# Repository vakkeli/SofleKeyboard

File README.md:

# Sofle Keyboard Vakkeli fork

Own version off the great keyboard. Added 7th column to better support ISO and Nordic layout. Will be updating this readme. PCB is in prototype production at this point. Hopefully adding 3D printed plates, case and models for them.

# Original Sofle Keyboard

Sofle is 6×4+5 keys column-staggered split keyboard with encoder support. Based on [Lily58](https://github.com/kata0510/Lily58), [Corne](https://github.com/foostan/crkbd) and [Helix](https://github.com/MakotoKurauchi/helix) keyboards.

**[For more information and documentation visit https://josefadamcik.github.io/SofleKeyboard/](https://josefadamcik.github.io/SofleKeyboard/)**

SofleKeyboard was created by [Josef Adamcik](https://josef-adamcik.cz/). The motivation and process is covered in following blog-post: [Let me introduce you SofleKeyboard - a split keyboard based on Lily58 and Crkbd](https://josef-adamcik.cz/electronics/let-me-introduce-you-sofle-keyboard-split-keyboard-based-on-lily58.html)

Sofle RGB was contributed by [Dane Evans](https://github.com/DaneEvans).

## Firmware

Sofle uses [QMK firmware](https://qmk.fm/)

## Default layout

## Images of keyboard

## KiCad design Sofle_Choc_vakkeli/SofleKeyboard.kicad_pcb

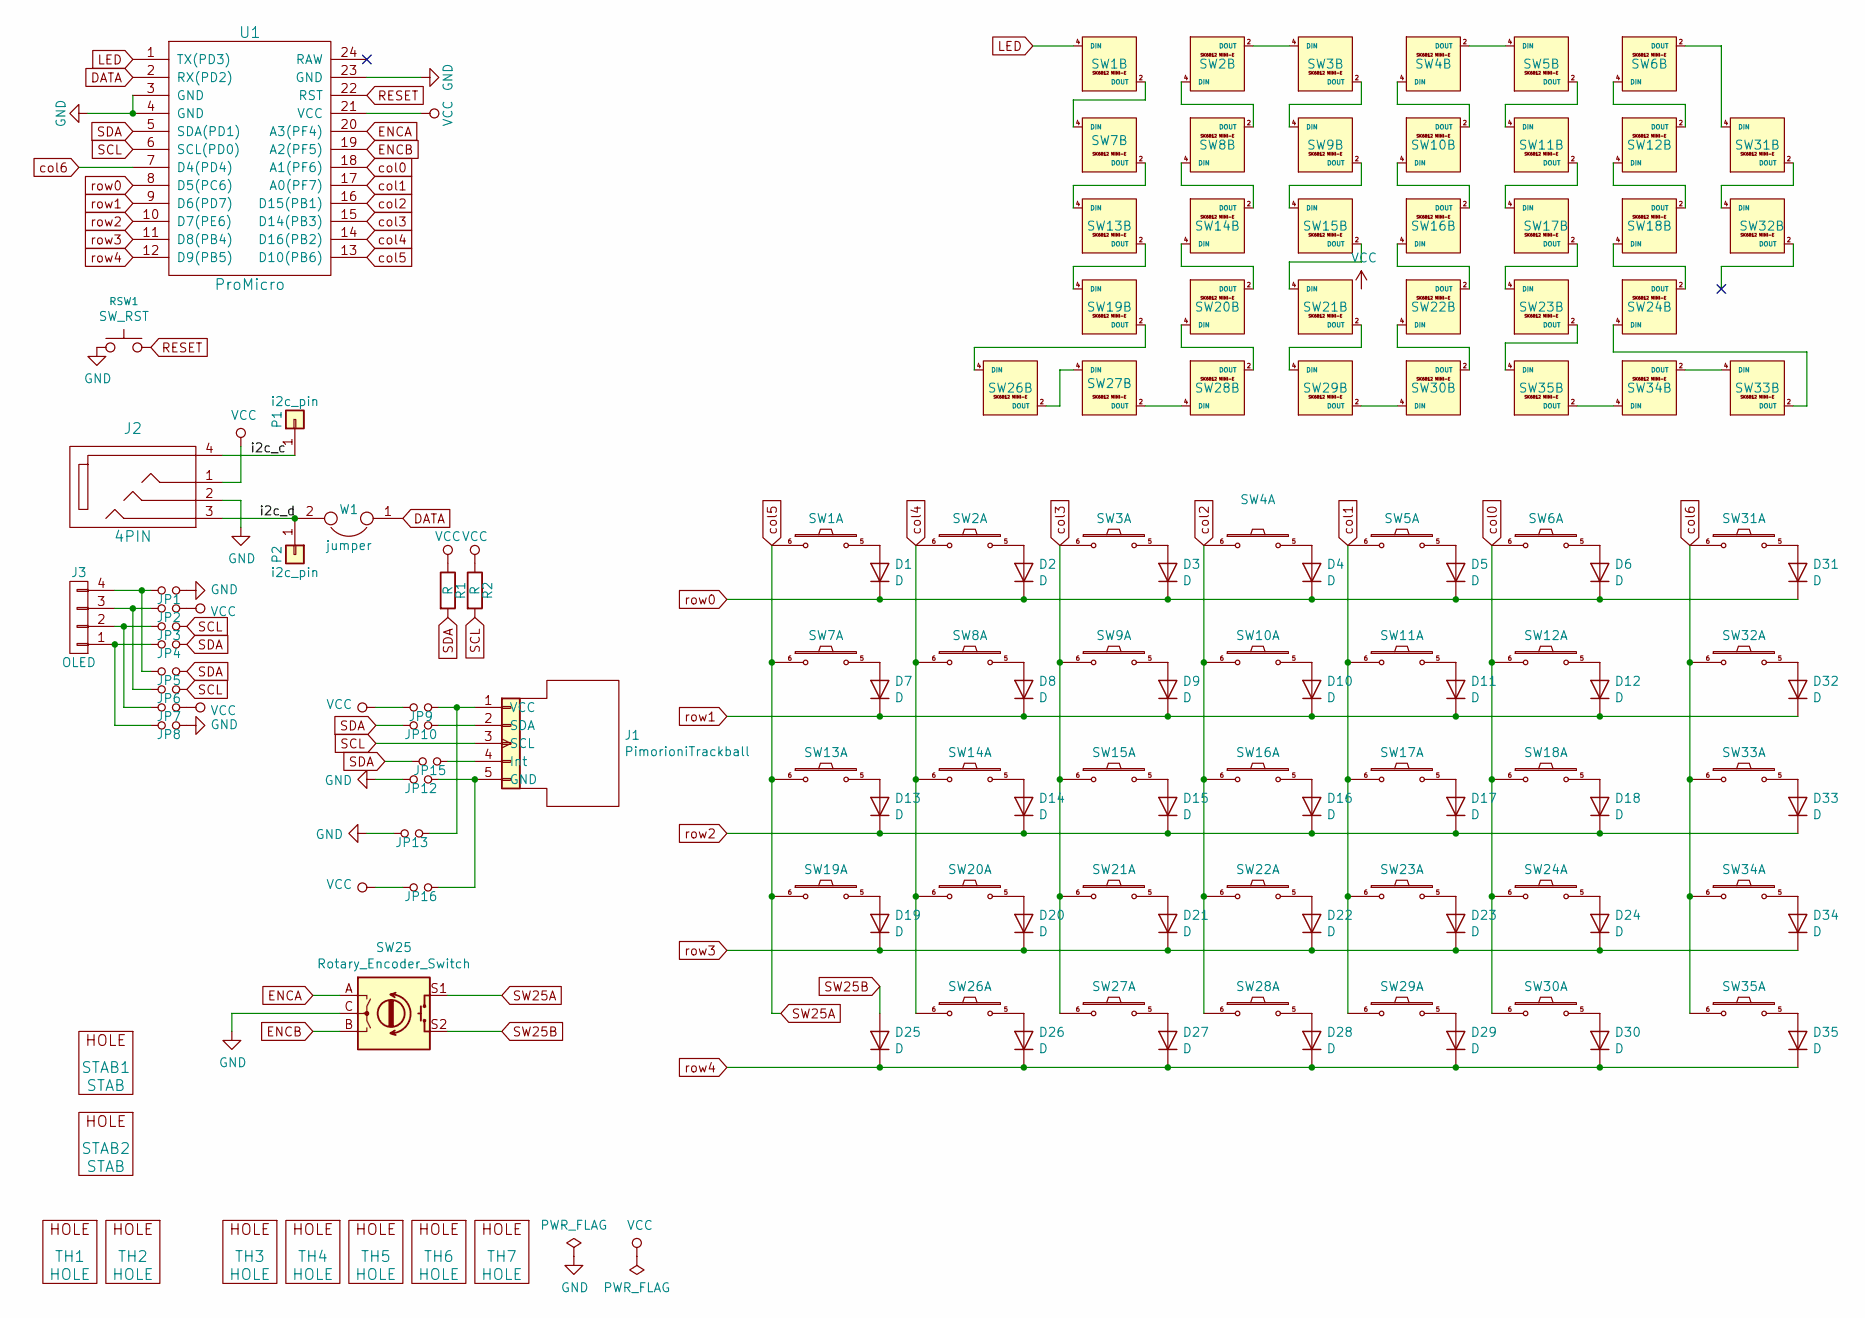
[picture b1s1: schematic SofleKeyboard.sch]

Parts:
D1, D2, D3, D4, D5, D6, D7, D8, D9, D10, D11, D12, D13, D14, D15, D16, D17, D18, D19, D20, D21, D22, D23, D24, D25, D26, D27, D28, D29, D30, D31, D32, D33, D34, D35: D; crkbd-diode
J1: PimorioniTrackball; pimoroni_trackball
J2: 4PIN; MJ-4PP-9
J3: OLED; OLED_4Pin
JP1, JP2, JP3, JP4, JP5, JP6, JP7, JP8, JP9, JP10, JP12, JP13, JP15, JP16: Jumper_NO_Small; Jumper
P1, P2: i2c_pin; 1pin_conn
R1, R2: R; RESISTOR_mini
RSW1: SW_RST; TACT_SWITCH_TVBP06
STAB1, STAB2: STAB; Kailh-PG1350-2u-stab
SW1, SW2, SW3, SW4, SW5, SW6, SW7, SW8, SW9, SW10, SW11, SW12, SW13, SW14, SW15, SW16, SW17, SW18, SW19, SW20, SW21, SW22, SW23, SW24, SW26, SW27, SW28, SW29, SW30, SW31, SW32, SW33, SW34, SW35: SW_PUSH_LED; Choc_Hotswap_SK6812MiniE
SW25: Rotary_Encoder_Switch; RotaryEncoder_Alps_EC11E-Switch_Vertical_H20mm-keebio_modif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
TH1, TH2: HOLE; M2_HOLE_PCB
TH3, TH4, TH5, TH6, TH7: HOLE; HOLE_M2_TH
U1: ProMicro
W1: jumper; jumper_data

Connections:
/i2c_c: J2.4, P1.1
/i2c_d: J2.3, P2.1, W1.2
DATA: U1.2 (RX(PD2)), W1.1
ENCA: SW3.C, SW25.A, U1.20 (A3(PF4))
ENCB: SW3.B, SW25.B, U1.19 (A2(PF5))
GND: J2.2, JP1.2, JP8.2, JP12.1, JP13.1, RSW1.1, SW1.3 (GND), SW2.3 (GND), SW3.A, SW4.3 (GND), SW5.3 (GND), SW6.3 (GND), SW7.3 (GND), SW8.3 (GND), SW9.3 (GND), SW10.3 (GND), SW11.3 (GND), SW12.3 (GND), SW13.3 (GND), SW14.3 (GND), SW15.3 (GND), SW16.3 (GND), SW17.3 (GND), SW18.3 (GND), SW19.3 (GND), SW20.3 (GND), SW21.3 (GND), SW22.3 (GND), SW23.3 (GND), SW24.3 (GND), SW25.C, SW26.3 (GND), SW27.3 (GND), SW28.3 (GND), SW29.3 (GND), SW30.3 (GND), SW31.3 (GND), SW32.3 (GND), SW33.3 (GND), SW34.3 (GND), SW35.3 (GND), U1.3 (GND), U1.4 (GND), U1.23 (GND); also elsewhere on the board
LED: SW1.4 (DIN), U1.1 (TX(PD3))
unnamed: D1.2 (A), SW1.5
unnamed: D2.2 (A), SW2.5
unnamed 9: D3.2 (A), SW3.5; also elsewhere on the board
unnamed: D4.2 (A), SW4.5
unnamed: D5.2 (A), SW5.5
unnamed: D6.2 (A), SW6.5
unnamed: D7.2 (A), SW7.5
unnamed: D8.2 (A), SW8.5
unnamed: D9.2 (A), SW9.5
unnamed: D10.2 (A), SW10.5
unnamed: D11.2 (A), SW11.5
unnamed: D12.2 (A), SW12.5
unnamed: D13.2 (A), SW13.5
unnamed: D14.2 (A), SW14.5
unnamed: D15.2 (A), SW15.5
unnamed: D16.2 (A), SW16.5
unnamed: D17.2 (A), SW17.5
unnamed: D18.2 (A), SW18.5
unnamed: D19.2 (A), SW19.5
unnamed: D20.2 (A), SW20.5
unnamed: D21.2 (A), SW21.5
unnamed: D22.2 (A), SW22.5
unnamed: D23.2 (A), SW23.5
unnamed: D24.2 (A), SW24.5
unnamed: D26.2 (A), SW26.5
unnamed: D27.2 (A), SW27.5
unnamed: D28.2 (A), SW28.5
unnamed: D29.2 (A), SW29.5
unnamed: D30.2 (A), SW30.5
unnamed: D31.2 (A), SW31.5
unnamed: D32.2 (A), SW32.5
unnamed: D33.2 (A), SW33.5
unnamed: D34.2 (A), SW34.5
unnamed: D35.2 (A), SW35.5
unnamed: J1.1 (VCC), JP9.2, JP13.2
unnamed: J1.2 (SDA), JP10.2
unnamed: J1.4 (Int), JP15.2
unnamed: J1.5 (GND), JP12.2, JP16.2
unnamed: J3.1, JP4.1, JP8.1
unnamed: J3.2, JP3.1, JP7.1
unnamed: J3.3, JP2.1, JP6.1
unnamed: J3.4, JP1.1, JP5.1
unnamed: SW1.2 (DOUT), SW7.4 (DIN)
unnamed 50: SW2.2 (DOUT), SW3.4 (DIN); also elsewhere on the board
unnamed: SW2.4 (DIN), SW8.2 (DOUT)
unnamed 52: SW3.2 (DOUT), SW9.4 (DIN); also elsewhere on the board
unnamed: SW4.2 (DOUT), SW5.4 (DIN)
unnamed: SW4.4 (DIN), SW10.2 (DOUT)
unnamed: SW10.4 (DIN), SW16.2 (DOUT)
unnamed: SW11.2 (DOUT), SW17.4 (DIN)
unnamed: SW5.2 (DOUT), SW11.4 (DIN)
unnamed: SW6.4 (DIN), SW12.2 (DOUT)
unnamed: SW12.4 (DIN), SW18.2 (DOUT)
unnamed: SW13.2 (DOUT), SW19.4 (DIN)
unnamed: SW7.2 (DOUT), SW13.4 (DIN)
unnamed: SW8.4 (DIN), SW14.2 (DOUT)
unnamed: SW14.4 (DIN), SW20.2 (DOUT)
unnamed: SW15.2 (DOUT), SW21.4 (DIN)
unnamed: SW9.2 (DOUT), SW15.4 (DIN)
unnamed: SW16.4 (DIN), SW22.2 (DOUT)
unnamed: SW17.2 (DOUT), SW23.4 (DIN)
unnamed: SW18.4 (DIN), SW24.2 (DOUT)
unnamed: SW19.2 (DOUT), SW26.4 (DIN)
unnamed: SW20.4 (DIN), SW28.2 (DOUT)
unnamed: SW21.2 (DOUT), SW29.4 (DIN)
unnamed: SW22.4 (DIN), SW30.2 (DOUT)
unnamed: SW23.2 (DOUT), SW35.4 (DIN)
unnamed: SW24.4 (DIN), SW33.2 (DOUT)
unnamed: SW26.2 (DOUT), SW27.4 (DIN)
unnamed: SW27.2 (DOUT), SW28.4 (DIN)
unnamed: SW29.2 (DOUT), SW30.4 (DIN)
unnamed: SW31.2 (DOUT), SW32.4 (DIN)
unnamed: SW6.2 (DOUT), SW31.4 (DIN)
unnamed: SW33.4 (DIN), SW34.2 (DOUT)
unnamed: SW34.4 (DIN), SW35.2 (DOUT)
RESET: RSW1.2, U1.22 (RST)
SCL: J1.3 (SCL), JP3.2, JP6.2, R2.2, U1.6 (SCL(PD0))
SDA: JP4.2, JP5.2, JP10.1, JP15.1, R1.2, U1.5 (SDA(PD1))
SW25A: SW1.6, SW3.S1, SW7.6, SW13.6, SW19.6, SW25.S1, U1.13 (D10(PB6))
SW25B: D25.2 (A), SW3.S2, SW25.S2
VCC: J2.1, JP2.2, JP7.2, JP9.1, JP16.1, R1.1, R2.1, SW1.1 (VDD), SW2.1 (VDD), SW4.1 (VDD), SW5.1 (VDD), SW6.1 (VDD), SW7.1 (VDD), SW8.1 (VDD), SW9.1 (VDD), SW10.1 (VDD), SW11.1 (VDD), SW12.1 (VDD), SW13.1 (VDD), SW14.1 (VDD), SW15.1 (VDD), SW16.1 (VDD), SW17.1 (VDD), SW18.1 (VDD), SW19.1 (VDD), SW20.1 (VDD), SW21.1 (VDD), SW22.1 (VDD), SW23.1 (VDD), SW24.1 (VDD), SW26.1 (VDD), SW27.1 (VDD), SW28.1 (VDD), SW29.1 (VDD), SW30.1 (VDD), SW31.1 (VDD), SW32.1 (VDD), SW33.1 (VDD), SW34.1 (VDD), SW35.1 (VDD), U1.21 (VCC); also elsewhere on the board
col0: SW6.6, SW12.6, SW18.6, SW24.6, SW30.6, U1.18 (A1(PF6))
col1: SW5.6, SW11.6, SW17.6, SW23.6, SW29.6, U1.17 (A0(PF7))
col2: SW4.6, SW10.6, SW16.6, SW22.6, SW28.6, U1.16 (D15(PB1))
col3: SW3.6, SW9.6, SW15.6, SW21.6, SW27.6, U1.15 (D14(PB3)); also elsewhere on the board
col4: SW2.6, SW8.6, SW14.6, SW20.6, SW26.6, U1.14 (D16(PB2))
col6: SW31.6, SW32.6, SW33.6, SW34.6, SW35.6, U1.7 (D4(PD4))
row0: D1.1 (K), D2.1 (K), D3.1 (K), D4.1 (K), D5.1 (K), D6.1 (K), D31.1 (K), U1.8 (D5(PC6))
row1: D7.1 (K), D8.1 (K), D9.1 (K), D10.1 (K), D11.1 (K), D12.1 (K), D32.1 (K), U1.9 (D6(PD7))
row2: D13.1 (K), D14.1 (K), D15.1 (K), D16.1 (K), D17.1 (K), D18.1 (K), D33.1 (K), U1.10 (D7(PE6))
row3: D19.1 (K), D20.1 (K), D21.1 (K), D22.1 (K), D23.1 (K), D24.1 (K), D34.1 (K), U1.11 (D8(PB4))
row4: D25.1 (K), D26.1 (K), D27.1 (K), D28.1 (K), D29.1 (K), D30.1 (K), D35.1 (K), U1.12 (D9(PB5))

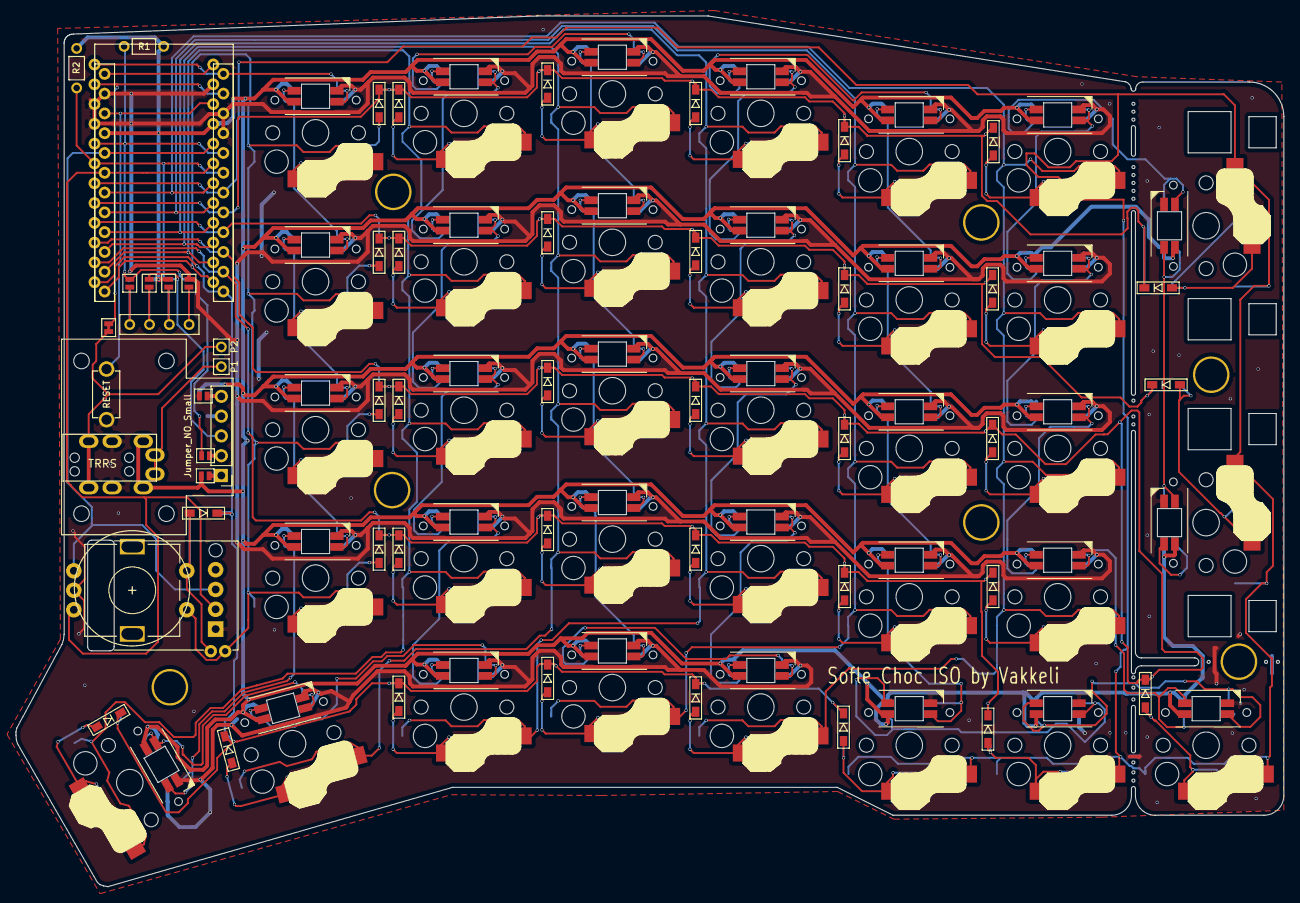
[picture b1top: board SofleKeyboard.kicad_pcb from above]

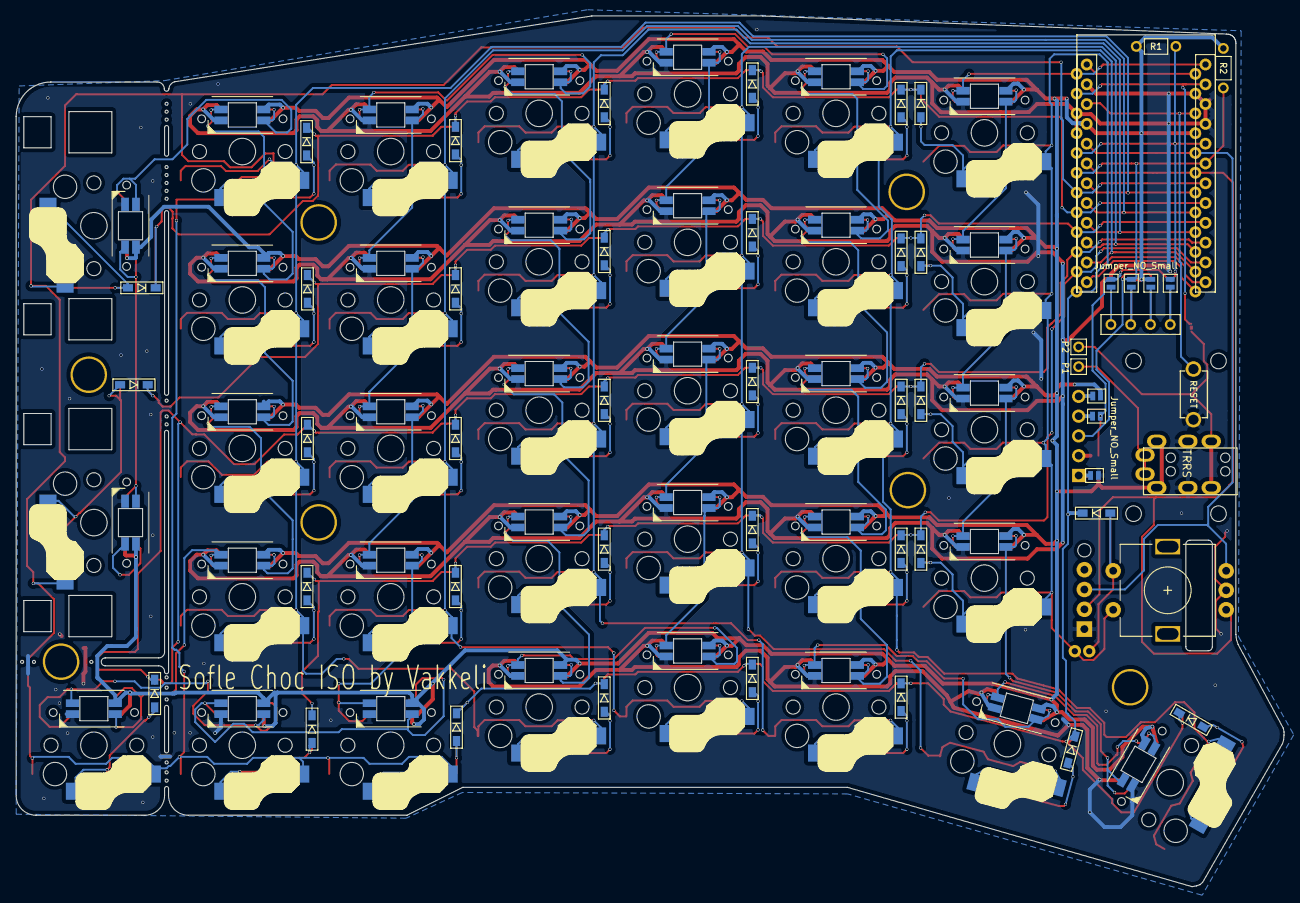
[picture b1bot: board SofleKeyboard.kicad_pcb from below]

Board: 2 copper layers, 162.7 x 111.8 mm, 104 parts (7 on the bottom side), 99 nets.

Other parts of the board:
SW3#2: SW_PUSH_LED; Choc_Hotswap_SK6812MiniE
TH6#2, TH6#3: HOLE; HOLE_M2_TH

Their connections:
GND: SW3#2.3; also elsewhere on the board
unnamed 9: SW3#2.5; also elsewhere on the board
unnamed 50: SW3#2.4; also elsewhere on the board
unnamed 52: SW3#2.2; also elsewhere on the board
VCC: SW3#2.1; also elsewhere on the board
col3: SW3#2.6; also elsewhere on the board

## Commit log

2022-01-18 First version of mod
2022-01-18 fixes, stabs, breakaways
2022-02-08 fixed single breakable button gnd, added dxf for 3d.
2022-02-08 fixed single button led order
2022-03-03 Fixes to pcb. Added functioning, but incomplete fw
